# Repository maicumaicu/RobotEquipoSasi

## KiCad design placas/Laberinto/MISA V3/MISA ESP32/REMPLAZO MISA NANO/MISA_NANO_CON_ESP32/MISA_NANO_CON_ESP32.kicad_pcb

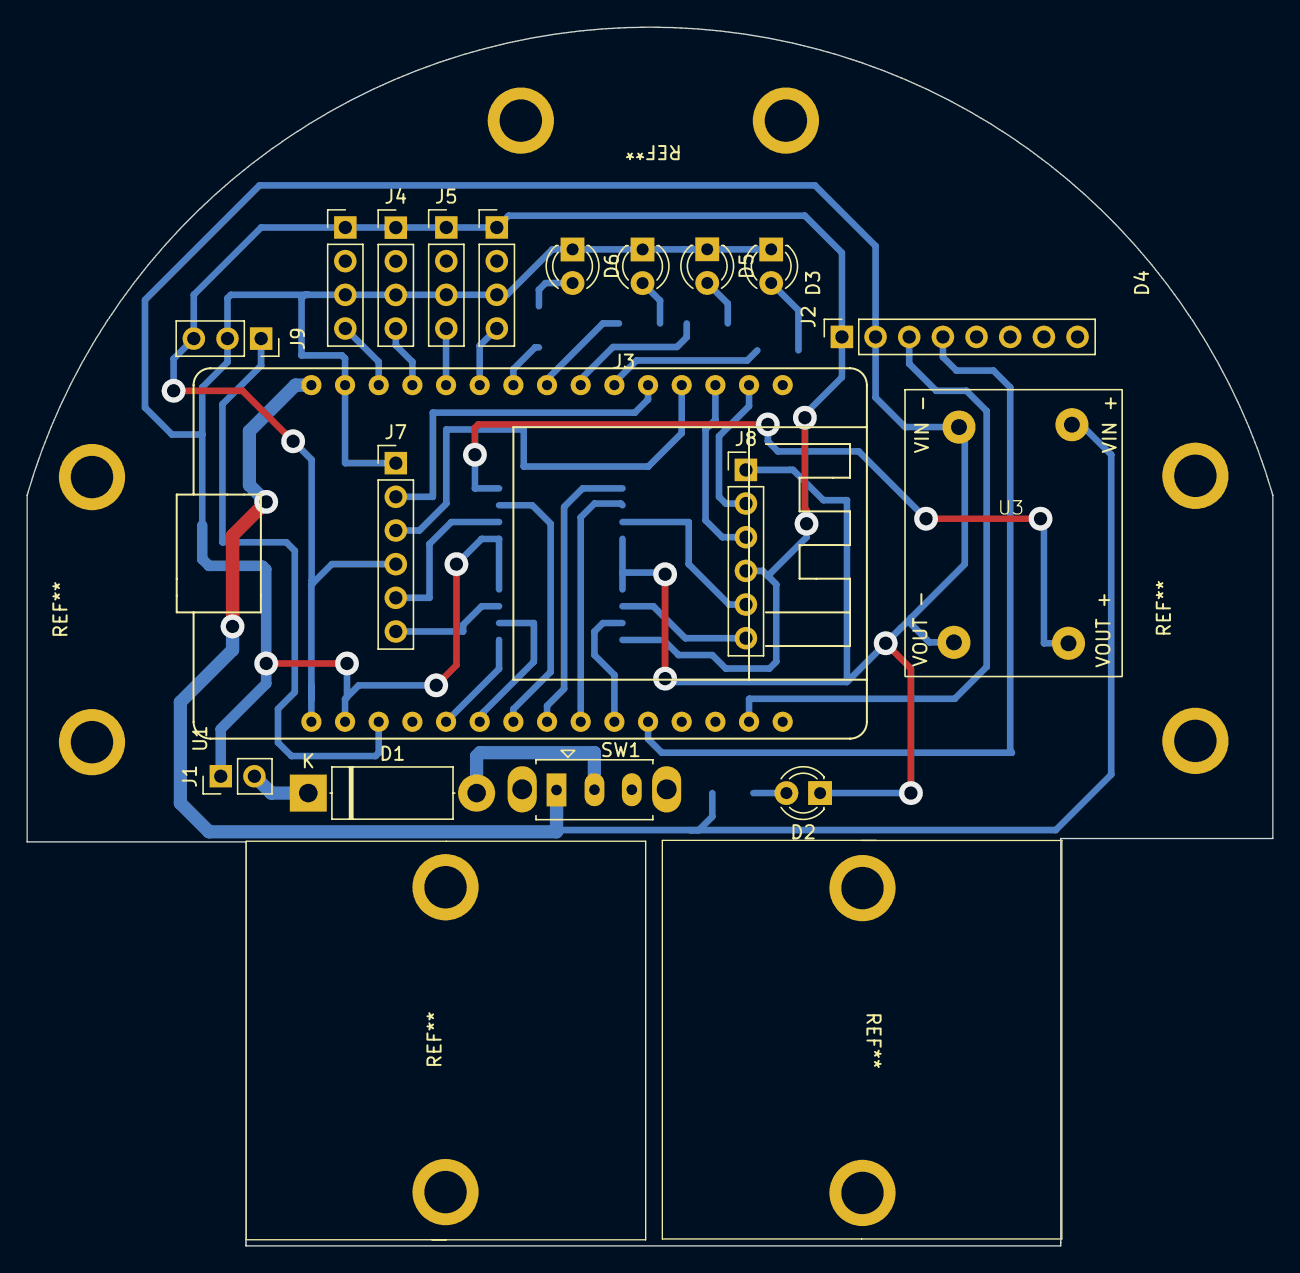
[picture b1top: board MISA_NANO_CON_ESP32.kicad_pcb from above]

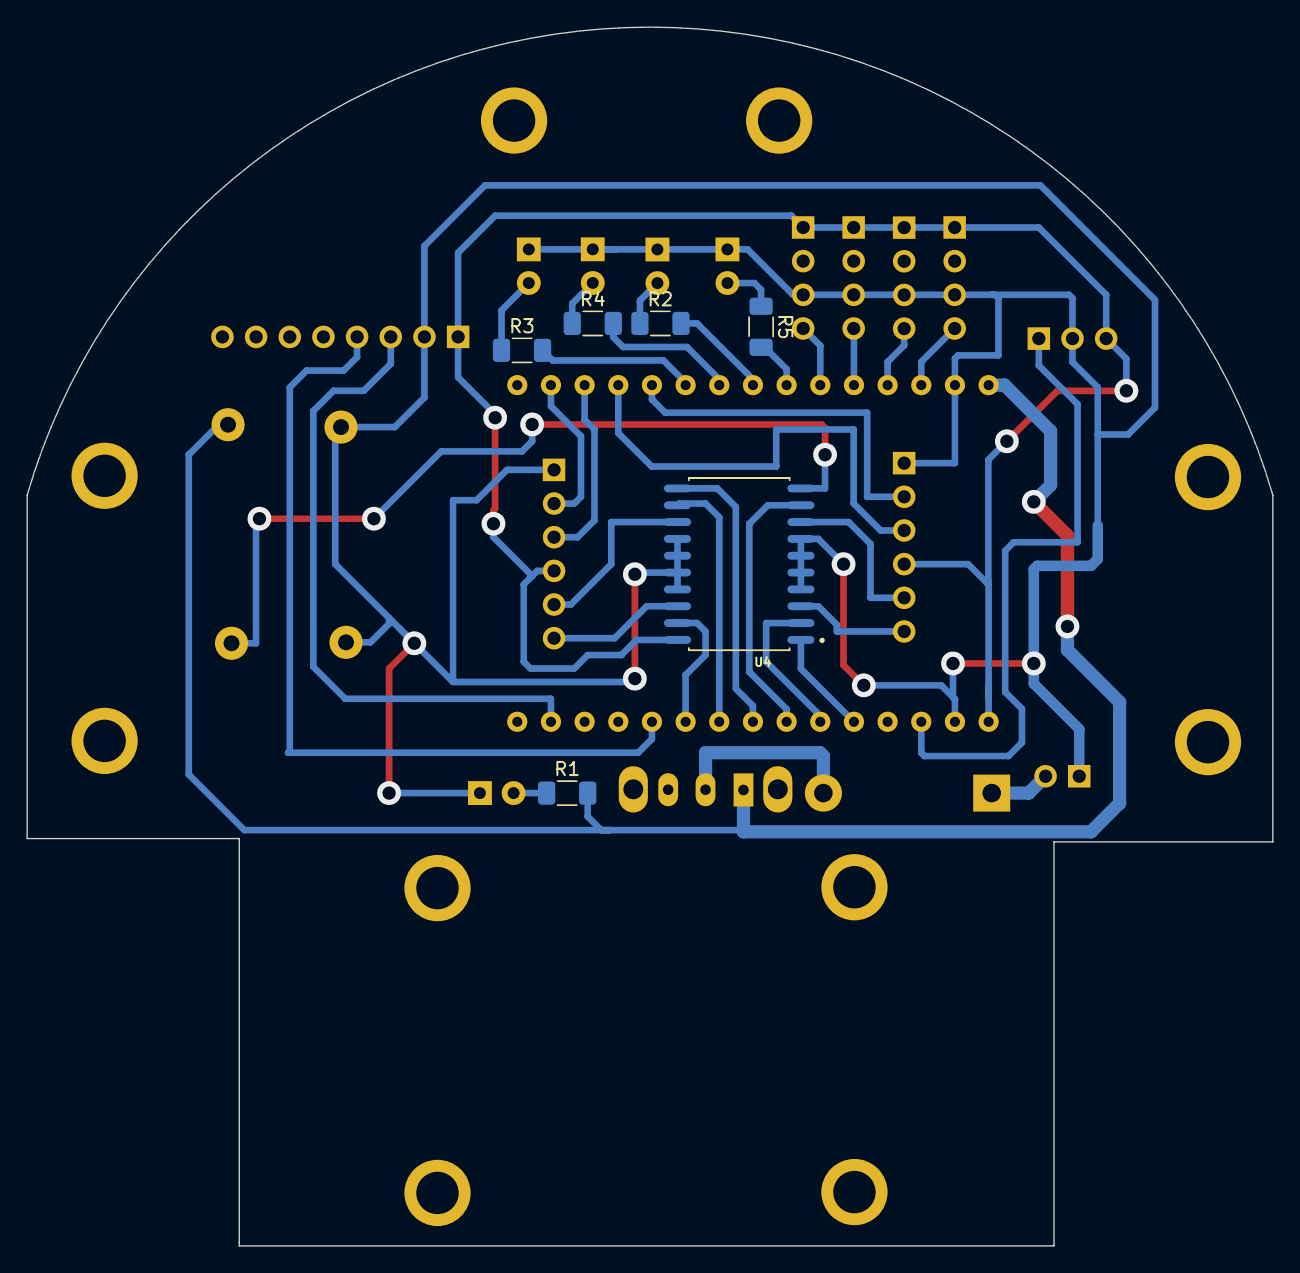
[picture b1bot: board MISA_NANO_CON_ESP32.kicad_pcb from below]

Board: 2 copper layers, 94.0 x 91.9 mm, 24 parts (6 on the bottom side), 36 nets.

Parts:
D1: type="D" model="DIODE" lib=""; D_5W_P12.70mm_Horizontal
D2, D3, D4, D5, D6: LED; LED_D3.0mm
J1: Conn_01x02_Male; PinHeader_1x02_P2.54mm_Vertical
J2: Conn_01x08_Female; PinSocket_1x08_P2.54mm_Vertical
J3, J4, J5, J6: Conn_01x04_Male; PinHeader_1x04_P2.54mm_Vertical
J7, J8: Conn_01x06_Female; PinHeader_1x06_P2.54mm_Vertical
J9: Conn_01x03_Socket; PinSocket_1x03_P2.54mm_Vertical
R1, R2, R3, R4, R5: R; R_1206_3216Metric_Pad1.30x1.75mm_HandSolder
SW1: SW_DPDT_x2; SW_Slide_1P2T_CK_OS102011MS2Q
U1: ESP32-Devkit-V1; DOIT_ESP32_Devkit
U3: Mt3608; Sx1308
U4: L293DD; SOIC127P1032X265-20N

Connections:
/3.3V: J2.1, J3.1, J4.1, J5.1, J6.1, J7.4, J8.4, J9.3, U1.30 (3v3), U4.20 (VSS)
/AO1: J7.6, U4.3 (OUTPUT_1)
/AO2: J7.5, U4.8 (OUTPUT_2)
/BO1: J8.5, U4.13 (OUTPUT_3)
/BO2: J8.6, U4.18 (OUTPUT_4)
/CNY70: J6.4, U1.3 (IO13)
/INA1: U1.25 (IO16), U4.2 (INPUT_1)
/INA2: U1.24 (IO17), U4.9 (INPUT_2)
/INB1: U1.21 (IO19), U4.19 (INPUT_4)
/INB2: U1.22 (IO18), U4.12 (INPUT_3)
/IR: J9.1, U1.28 (IO15)
/L1: R2.2, U1.8 (IO25)
/L2: R3.2, U1.10 (IO32)
/L3: R4.2, U1.9 (IO33)
/L4: R5.2, U1.7 (IO26)
/MA1: J7.2, U1.11 (IO35)
/MA2: J7.3, U1.12 (IO34)
/MB1: J8.2, U1.14 (IO36)
/MB2: J8.3, U1.13 (IO39)
/PWM1: U1.26 (IO4), U4.1 (ENABLE_1)
/PWM2: U1.23 (IO5), U4.11 (ENABLE_2)
/SCL: J2.3, U1.17 (IO22)
/SDA: J2.4, U1.20 (IO21)
/SHARP_C: J5.4, U1.5 (IO14)
/SHARP_D: J3.4, U1.6 (IO27)
/SHARP_I: J4.4, U1.4 (IO12)
/VIn: R1.2, SW1.1 (A), U1.1 (Vin), U3.1 (VIN+)
/Vm: U3.2 (VOUT+), U4.10 (VS)
GND: D2.1 (K), D3.1 (K), D4.1 (K), D5.1 (K), D6.1 (K), J1.1, J2.2, J3.3, J4.3, J5.3, J6.3, J7.1, J8.1, J9.2, U1.2 (GND), U1.29 (GND), U3.3 (VIN-), U3.4 (VOUT-), U4.4 (GND), U4.5 (GND), U4.6 (GND), U4.7 (GND), U4.14 (GND), U4.15 (GND), U4.16 (GND), U4.17 (GND)
unnamed: D1.1 (A), J1.2
unnamed: D1.2 (K), SW1.2 (B)
unnamed: D2.2 (A), R1.1
unnamed: D3.2 (A), R2.1
unnamed: D4.2 (A), R3.1
unnamed: D5.2 (A), R4.1
unnamed: D6.2 (A), R5.1

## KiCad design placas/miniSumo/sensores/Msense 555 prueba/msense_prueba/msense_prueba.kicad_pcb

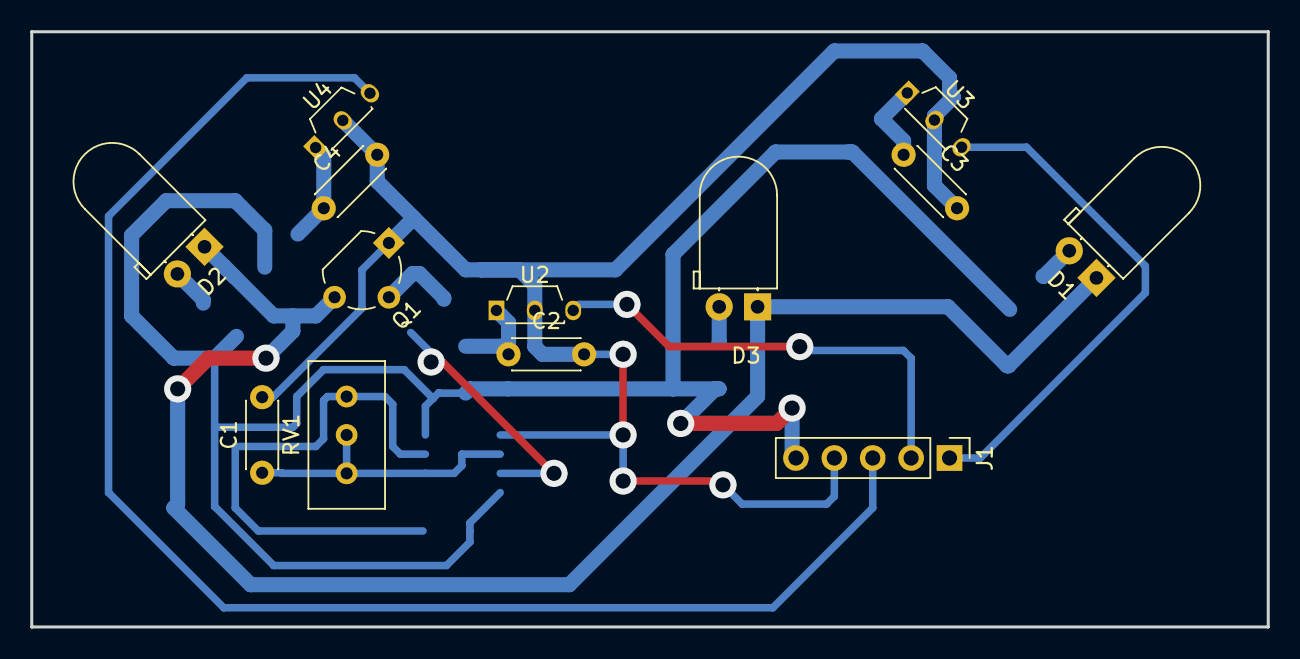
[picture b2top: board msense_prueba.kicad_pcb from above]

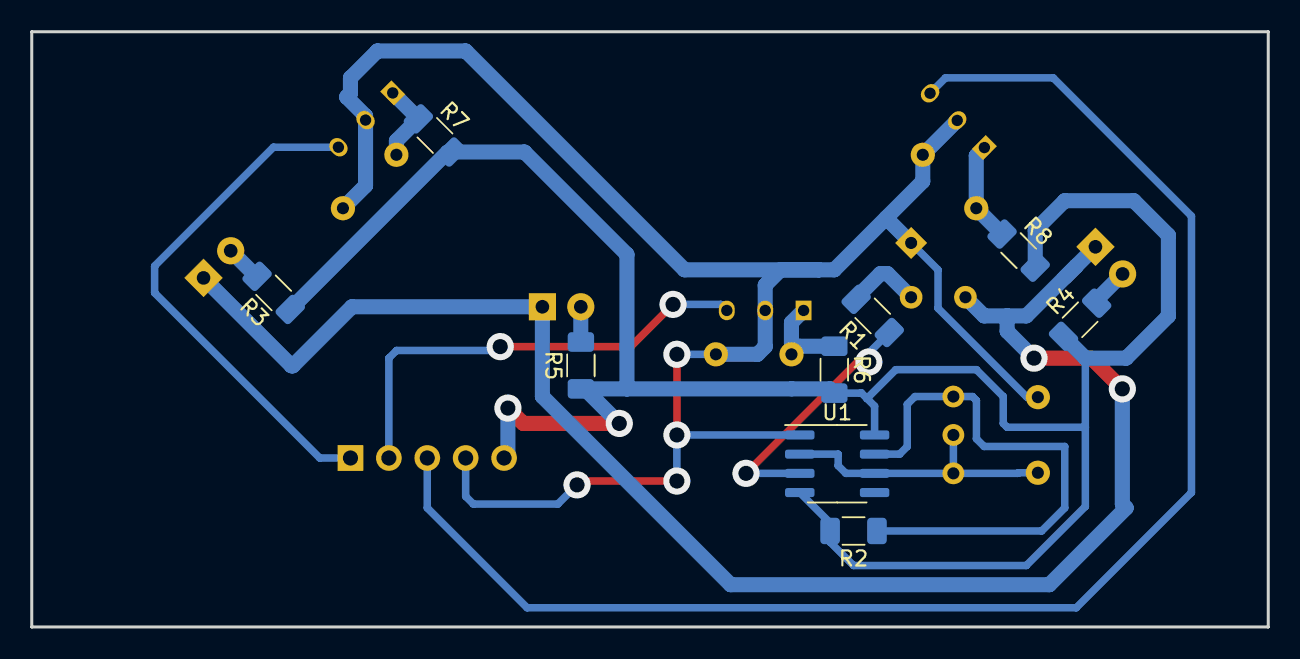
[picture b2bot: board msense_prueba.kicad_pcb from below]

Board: 2 copper layers, 81.8 x 39.4 mm, 22 parts (9 on the bottom side), 16 nets.

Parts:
C1: 102; C_Disc_D4.3mm_W1.9mm_P5.00mm
C2, C3, C4: 104; C_Disc_D4.3mm_W1.9mm_P5.00mm
D1, D2, D3: LED; LED_D5.0mm_Horizontal_O1.27mm_Z3.0mm
J1: Conn_01x05_Pin; PinHeader_1x05_P2.54mm_Vertical
Q1: BC547; TO-92_Wide
R1: 4.7k; R_1206_3216Metric_Pad1.30x1.75mm_HandSolder
R2: 1k8; R_1206_3216Metric_Pad1.30x1.75mm_HandSolder
R3, R4, R5, R6, R7, R8: 100; R_1206_3216Metric_Pad1.30x1.75mm_HandSolder
RV1: pote; Potentiometer_Bourns_3296W_Vertical
U1: LM555xM; SOIC-8_3.9x4.9mm_P1.27mm
U2, U3, U4: TSOP17xx; TO-92S_Wide

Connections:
38khz: D1.1 (K), D2.1 (K), D3.1 (K), Q1.3 (E)
+5V: J1.5, R2.2, R3.1, R4.1, R5.1, R6.2, R7.2, R8.2, U1.4 (R), U1.8 (VCC)
/S1: J1.3, U4.3 (OUT)
/S2: J1.2, U2.3 (OUT)
/S3: J1.1, U3.3 (OUT)
GND: C1.2, C2.2, C3.2, C4.2, J1.4, Q1.1 (C), U1.1 (GND), U2.2 (Vs), U3.2 (Vs), U4.2 (Vs)
unnamed: D1.2 (A), R3.2
unnamed: D2.2 (A), R4.2
unnamed: D3.2 (A), R5.2
unnamed: Q1.2 (B), R1.2
unnamed: R2.1, RV1.1, U1.7 (DIS)
unnamed: R1.1, U1.3 (Q)
unnamed: C1.1, RV1.2, RV1.3, U1.2 (TR), U1.6 (THR)
unnamed: C2.1, R6.1, U2.1 (GND)
unnamed: C3.1, R7.1, U3.1 (GND)
unnamed: C4.1, R8.1, U4.1 (GND)

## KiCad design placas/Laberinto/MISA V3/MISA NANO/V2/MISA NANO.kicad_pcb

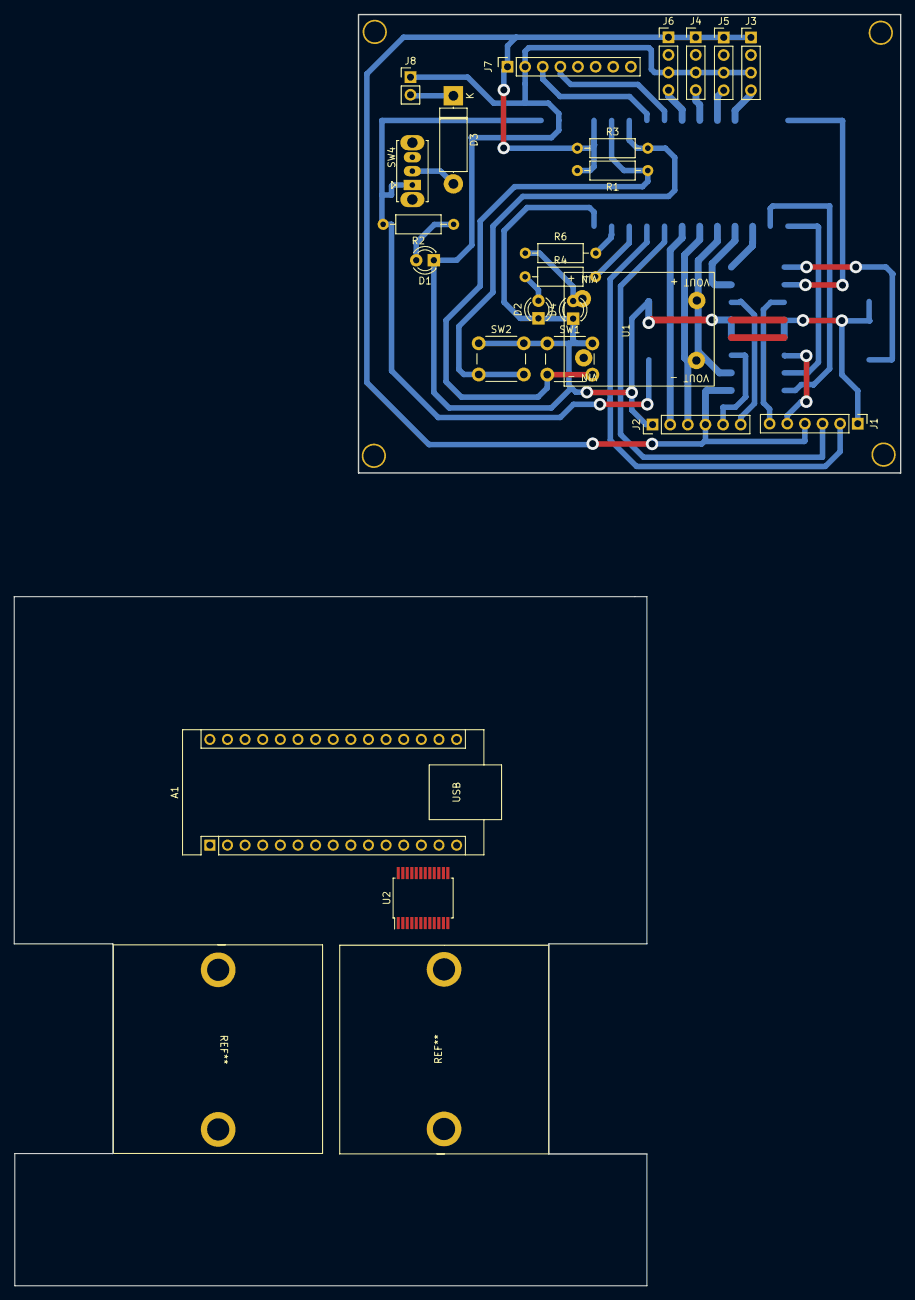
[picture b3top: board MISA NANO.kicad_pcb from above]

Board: 2 copper layers, 78.1 x 66.1 mm, 23 parts (0 on the bottom side), 33 nets.

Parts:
A1: Arduino_Nano_v3.x; Arduino_Nano
D1, D2, D4: LED; LED_D3.0mm
D3: type="D" model="DIODE" lib=""; D_5W_P12.70mm_Horizontal
J1, J2: Conn_01x06_Female; PinHeader_1x06_P2.54mm_Vertical
J3, J4, J5, J6: Conn_01x04_Male; PinHeader_1x04_P2.54mm_Vertical
J7: Conn_01x08_Female; PinSocket_1x08_P2.54mm_Vertical
J8: Conn_01x02_Male; PinHeader_1x02_P2.54mm_Vertical
R1, R2, R3, R4, R6: R; R_Axial_DIN0207_L6.3mm_D2.5mm_P10.16mm_Horizontal
SW1, SW2: SW_Push; SW_PUSH_6mm
SW4: SW_DPDT_x2; SW_Slide_1P2T_CK_OS102011MS2Q
U1: Mt3608; Sx1308
U2: TB6612FNG; SSOP-24_5.3x8.2mm_P0.65mm

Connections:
/5v: A1.27 (+5V), J1.4, J2.4, J3.1, J4.1, J5.1, J6.1, J7.1, R1.2, R3.1, U2.20 (VCC)
/AO1: J1.5, U2.1 (AO1), U2.2 (AO1)
/AO2: J1.6, U2.5 (AO2), U2.6 (AO2)
/BO1: J2.6, U2.11 (BO1), U2.12 (BO1)
/BO2: J2.5, U2.7 (BO2), U2.8 (BO2)
/BTN1: A1.26 (A7), R1.1, SW1.2
/BTN2: A1.25 (A6), R3.2, SW2.2
/CNY70: A1.22 (A3), J6.4
/INA1: A1.15 (D12), U2.21 (AIN1)
/INA2: A1.16 (D13), U2.22 (AIN2)
/INB1: A1.12 (D9), U2.17 (BIN1)
/INB2: A1.11 (D8), U2.16 (BIN2)
/Led: A1.6 (D3), R4.2
/Led2: A1.5 (D2), R6.2
/MA1: A1.7 (D4), J1.2
/MA2: A1.8 (D5), J1.3
/MB1: A1.9 (D6), J2.2
/MB2: A1.10 (D7), J2.3
/PWM1: A1.14 (D11), U2.23 (PWMA)
/PWM2: A1.13 (D10), U2.15 (PWMB)
/SCL: A1.24 (A5), J7.3
/SDA: A1.23 (A4), J7.4
/SHARP_C: A1.20 (A1), J5.4
/SHARP_D: A1.19 (A0), J3.4
/SHARP_I: A1.21 (A2), J4.4
/VIn: A1.30 (VIN), R2.2, SW4.1 (A), U1.1 (VIN+)
/Vm: U1.2 (VOUT+), U2.13 (VM2), U2.14 (VM3), U2.24 (VM1)
GND: A1.4 (GND), A1.29 (GND), D1.1 (K), D2.1 (K), D4.1 (K), J1.1, J2.1, J3.3, J4.3, J5.3, J6.3, J7.2, J8.1, SW1.1, SW2.1, U1.3 (VIN-), U1.4 (VOUT-), U2.3 (PGND1), U2.4 (PGND1), U2.9 (PGND2), U2.10 (PGND2), U2.18 (GND)
unnamed: D1.2 (A), R2.1
unnamed: D2.2 (A), R4.1
unnamed: D3.1 (A), J8.2
unnamed: D3.2 (K), SW4.2 (B)
unnamed: D4.2 (A), R6.1

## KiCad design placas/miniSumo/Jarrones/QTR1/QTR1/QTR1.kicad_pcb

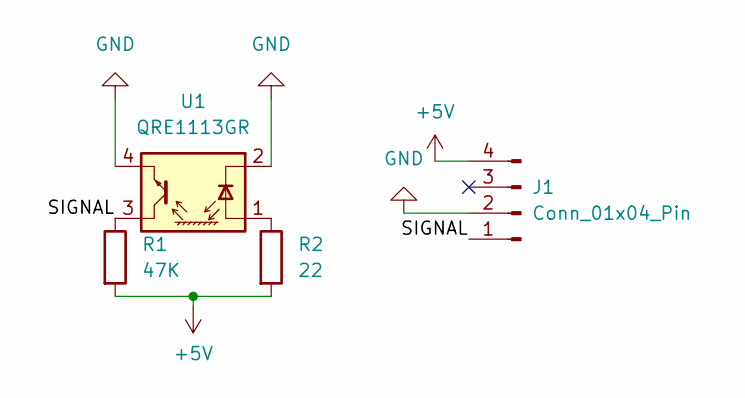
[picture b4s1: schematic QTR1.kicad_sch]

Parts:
J1: Conn_01x04_Pin; PinHeader_1x04_P2.54mm_Horizontal
R1: 47K; R_1206_3216Metric_Pad1.30x1.75mm_HandSolder
R2: 22; R_1206_3216Metric_Pad1.30x1.75mm_HandSolder
U1: QRE1113GR; OnSemi_CASE100CY

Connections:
+5V: J1.4, R1.2, R2.2
/SIGNAL: J1.1, R1.1, U1.3
GND: J1.2, U1.2 (K), U1.4
unnamed: R2.1, U1.1 (A)

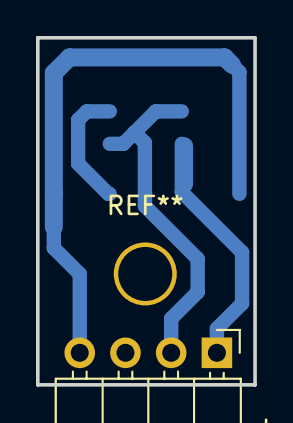
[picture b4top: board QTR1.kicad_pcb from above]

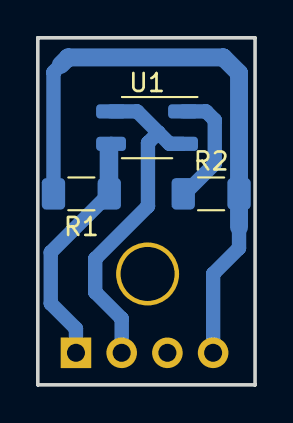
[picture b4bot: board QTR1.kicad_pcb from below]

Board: 2 copper layers, 12.1 x 19.3 mm, 4 parts (3 on the bottom side), 4 nets.

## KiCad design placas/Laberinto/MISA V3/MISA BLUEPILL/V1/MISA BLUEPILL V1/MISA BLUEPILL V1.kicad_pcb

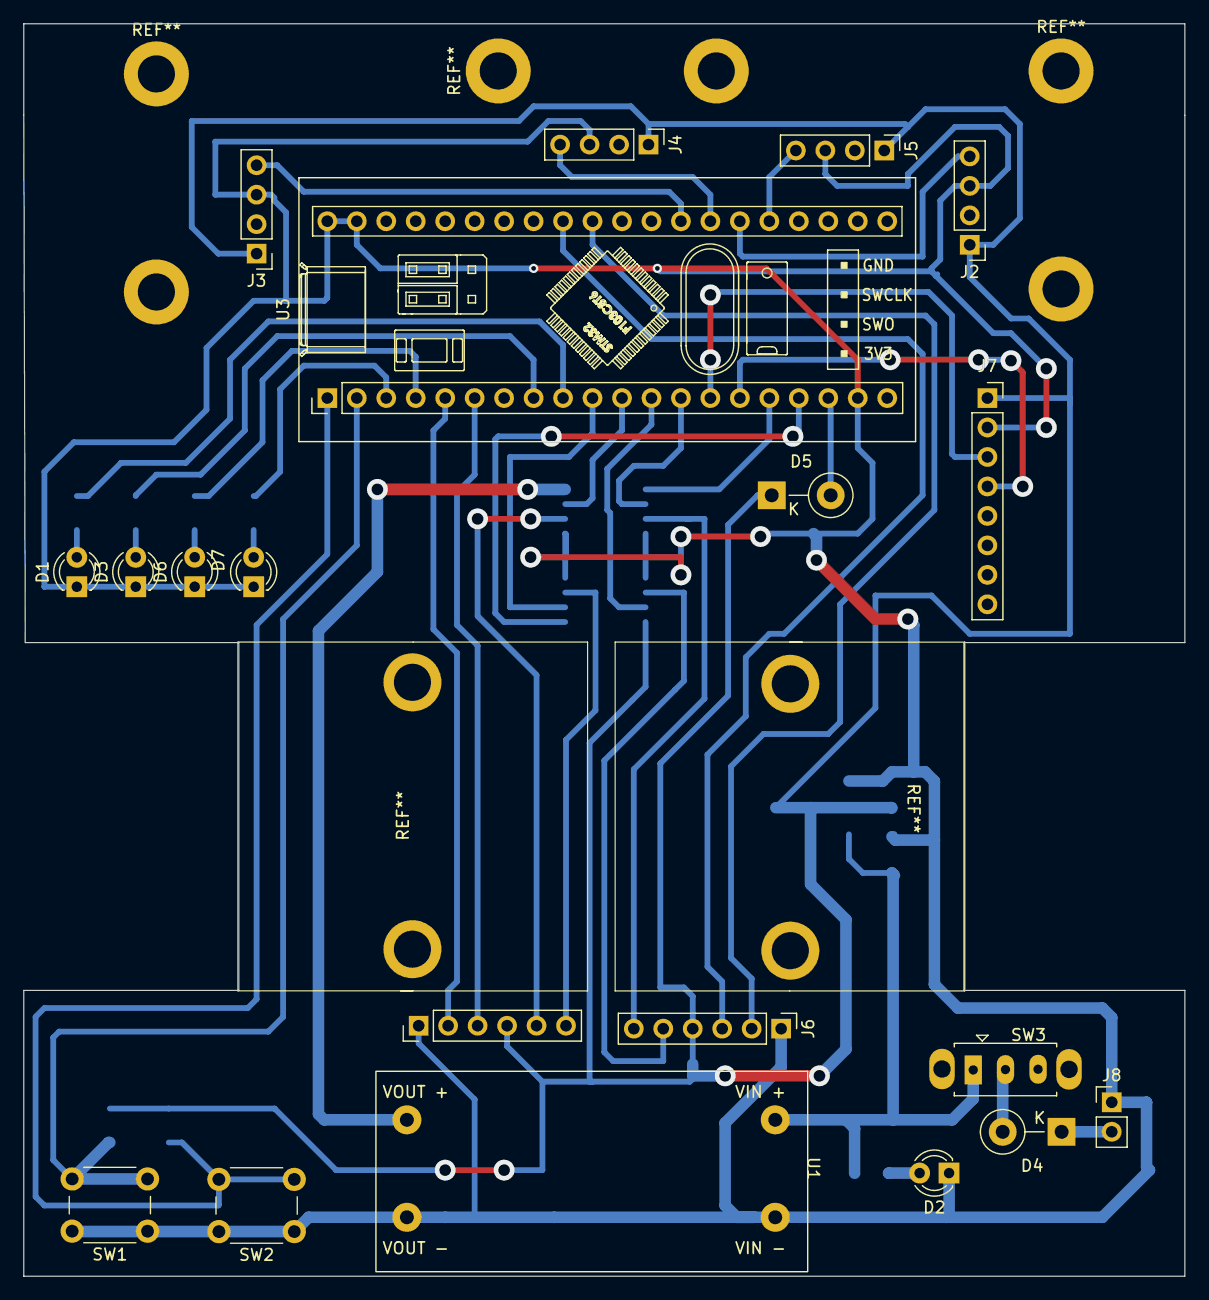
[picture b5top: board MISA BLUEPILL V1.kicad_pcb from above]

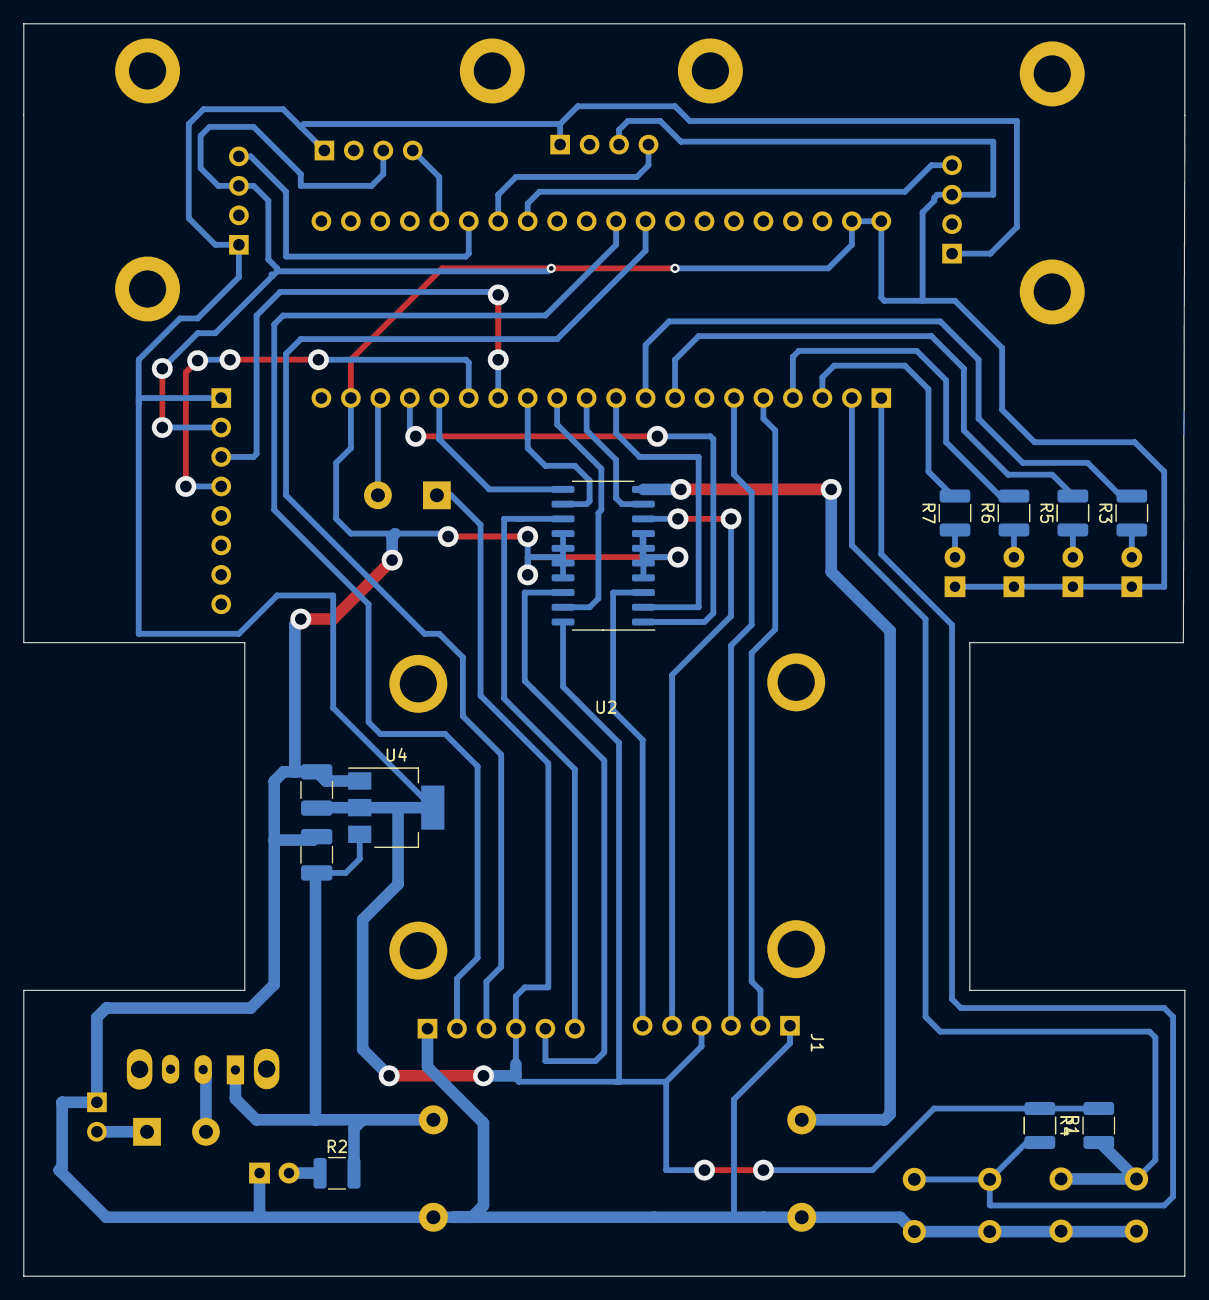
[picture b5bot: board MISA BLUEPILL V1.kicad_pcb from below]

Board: 2 copper layers, 100.1 x 107.9 mm, 31 parts (11 on the bottom side), 38 nets.

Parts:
C1, C2: C_Polarized; C_1210_3225Metric_Pad1.33x2.70mm_HandSolder
D1, D2, D3, D6, D7: LED; LED_D3.0mm
D4, D5: type="D" model="DIODE" lib=""; D_DO-15_P5.08mm_Vertical_KathodeUp
J1, J6: Conn_01x06_Female; PinHeader_1x06_P2.54mm_Vertical
J2, J3, J4, J5: Conn_01x04_Male; PinHeader_1x04_P2.54mm_Vertical
J7: Conn_01x08_Female; PinSocket_1x08_P2.54mm_Vertical
J8: Conn_01x02_Male; PinHeader_1x02_P2.54mm_Vertical
R1, R2, R3, R4, R5, R6, R7: R; R_1210_3225Metric
SW1, SW2: SW_Push; SW_PUSH_6mm
SW3: SW_DPDT_x2; SW_Slide_1P2T_CK_OS102011MS2Q
U1: Mt3608; MT3608
U2: L293; SO-20_5.3x12.6mm_P1.27mm
U3: YAAJ_BluePill_Part_Like_SWD_Breakout; YAAJ_BluePill_1
U4: AMS1117-5.0; SOT-223-3_TabPin2

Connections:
/5v: C2.1, D5.1 (A), J1.4, J2.1, J3.1, J4.1, J5.1, J6.4, J7.1, R1.2, R4.1, U2.20 (VCC1), U4.2 (VO)
/AO1: J1.5, U2.8 (2Y)
/AO2: J1.6, U2.3 (1Y)
/BO1: J6.6, U2.13 (3Y)
/BO2: J6.5, U2.18 (4Y)
/BTN1: R1.1, SW1.2, U3.2 (PB13)
/BTN2: R4.2, SW2.2, U3.1 (PB12)
/CNY70: J5.4, U3.25 (PA0)
/INA1: U2.2 (1A), U3.10 (PA15)
/INA2: U2.9 (2A), U3.11 (PB3)
/INB1: U2.12 (3A), U3.13 (PB5)
/INB2: U2.19 (4A), U3.12 (PB4)
/Led: R5.2, U3.8 (PA11)
/Led2: R3.2, U3.9 (PA12)
/Led3: R6.2, U3.4 (PB15)
/Led4: R7.2, U3.3 (PB14)
/MA1: J1.2, U3.5 (PA8)
/MA2: J1.3, U3.6 (PA9)
/MB1: J6.2, U3.31 (PA6)
/MB2: J6.3, U3.32 (PA7)
/PWM1: U2.1 (EN1,2), U3.17 (PB9)
/PWM2: U2.11 (EN3,4), U3.16 (PB8)
/SCL: J7.3, U3.14 (PB6)
/SDA: J7.4, U3.15 (PB7)
/SHARP_C: J4.4, U3.27 (PA2)
/SHARP_D: J2.4, U3.26 (PA1)
/SHARP_I: J3.4, U3.28 (PA3)
/VIn: C1.1, R2.2, SW3.1 (A), U1.1 (VIN+), U4.3 (VI)
/Vm: U1.2 (VOUT+), U2.10 (VCC2)
GND: C1.2, C2.2, D1.1 (K), D2.1 (K), D3.1 (K), D6.1 (K), D7.1 (K), J1.1, J2.3, J3.3, J4.3, J5.3, J6.1, J7.2, J8.1, SW1.1, SW2.1, U1.3 (VIN-), U1.4 (VOUT-), U2.4 (GND), U2.5 (GND), U2.6 (GND), U2.7 (GND), U2.14 (GND), U2.15 (GND), U2.16 (GND), U2.17 (GND), U3.19 (GND), U3.39 (GND), U3.40 (GND), U4.1 (GND)
unnamed: D1.2 (A), R3.1
unnamed: D2.2 (A), R2.1
unnamed: D3.2 (A), R5.1
unnamed: D4.1 (A), J8.2
unnamed: D4.2 (K), SW3.2 (B)
unnamed: D5.2 (K), U3.18 (5V)
unnamed: D6.2 (A), R6.1
unnamed: D7.2 (A), R7.1

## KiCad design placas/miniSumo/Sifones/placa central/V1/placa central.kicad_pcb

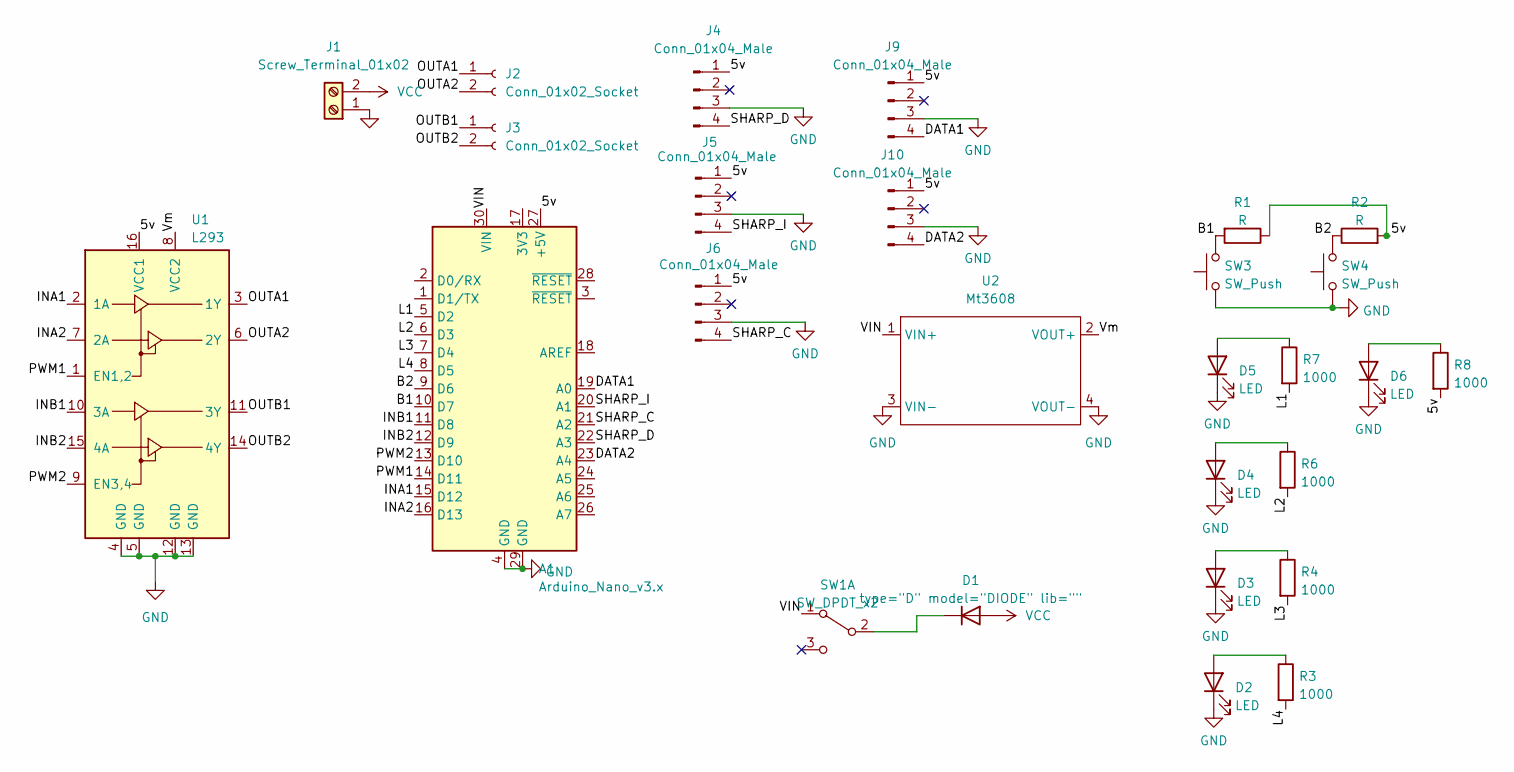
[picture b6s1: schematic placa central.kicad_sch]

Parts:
A1: Arduino_Nano_v3.x; Arduino_Nano
D1: type="D" model="DIODE" lib=""; D_5W_P5.08mm_Vertical_AnodeUp
D2, D3, D4, D5, D6: LED; LED_D3.0mm
J1: Screw_Terminal_01x02; PinSocket_1x02_P2.54mm_Vertical
J2, J3: Conn_01x02_Socket; PinSocket_1x02_P2.54mm_Vertical
J4, J5, J6, J9, J10: Conn_01x04_Male; PinHeader_1x04_P2.54mm_Vertical
R1, R2: R; R_1206_3216Metric_Pad1.30x1.75mm_HandSolder
R3, R4, R6, R7, R8: 1000; R_1206_3216Metric_Pad1.30x1.75mm_HandSolder
SW1: SW_DPDT_x2; SW_Slide_1P2T_CK_OS102011MS2Q
SW3, SW4: SW_Push; SW_PUSH_6mm
U1: L293; DIP-16_W7.62mm
U2: Mt3608; MT3608

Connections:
/5v: A1.27 (+5V), J4.1, J5.1, J6.1, J9.1, J10.1, R1.1, R2.2, R8.2, U1.16 (VCC1)
/B1: A1.10 (D7), R1.2, SW3.2
/B2: A1.9 (D6), R2.1, SW4.2
/DATA1: A1.19 (A0), J9.4
/DATA2: A1.23 (A4), J10.4
/INA1: A1.15 (D12), U1.2 (1A)
/INA2: A1.16 (D13), U1.7 (2A)
/INB1: A1.11 (D8), U1.10 (3A)
/INB2: A1.12 (D9), U1.15 (4A)
/L1: A1.5 (D2), R7.2
/L2: A1.6 (D3), R6.2
/L3: A1.7 (D4), R4.2
/L4: A1.8 (D5), R3.2
/OUTA1: J2.1, U1.3 (1Y)
/OUTA2: J2.2, U1.6 (2Y)
/OUTB1: J3.1, U1.11 (3Y)
/OUTB2: J3.2, U1.14 (4Y)
/PWM1: A1.14 (D11), U1.1 (EN1,2)
/PWM2: A1.13 (D10), U1.9 (EN3,4)
/SHARP_C: A1.21 (A2), J6.4
/SHARP_D: A1.22 (A3), J4.4
/SHARP_I: A1.20 (A1), J5.4
/VIN: A1.30 (VIN), SW1.1 (A), U2.1 (VIN+)
/Vm: U1.8 (VCC2), U2.2 (VOUT+)
GND: A1.4 (GND), A1.29 (GND), D2.1 (K), D3.1 (K), D4.1 (K), D5.1 (K), D6.1 (K), J1.1, J4.3, J5.3, J6.3, J9.3, J10.3, SW3.1, SW4.1, U1.4 (GND), U1.5 (GND), U1.12 (GND), U1.13 (GND), U2.3 (VIN-), U2.4 (VOUT-)
unnamed: D1.2 (K), SW1.2 (B)
unnamed: D2.2 (A), R3.1
unnamed: D3.2 (A), R4.1
unnamed: D4.2 (A), R6.1
unnamed: D5.2 (A), R7.1
unnamed: D6.2 (A), R8.1
VCC: D1.1 (A), J1.2

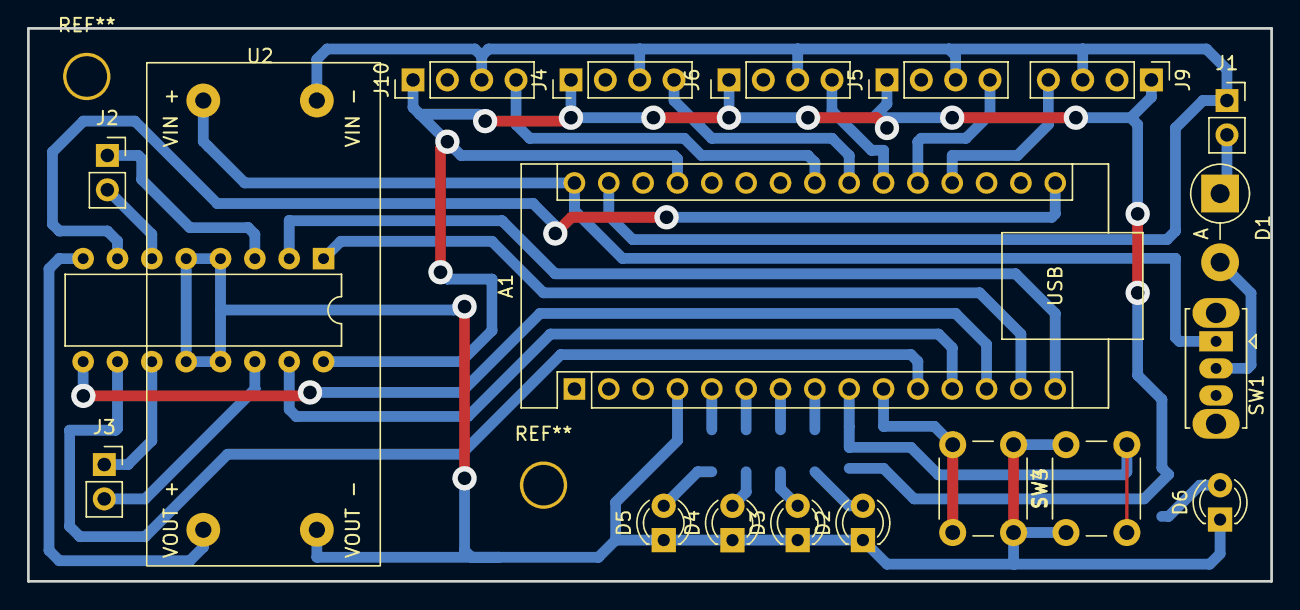
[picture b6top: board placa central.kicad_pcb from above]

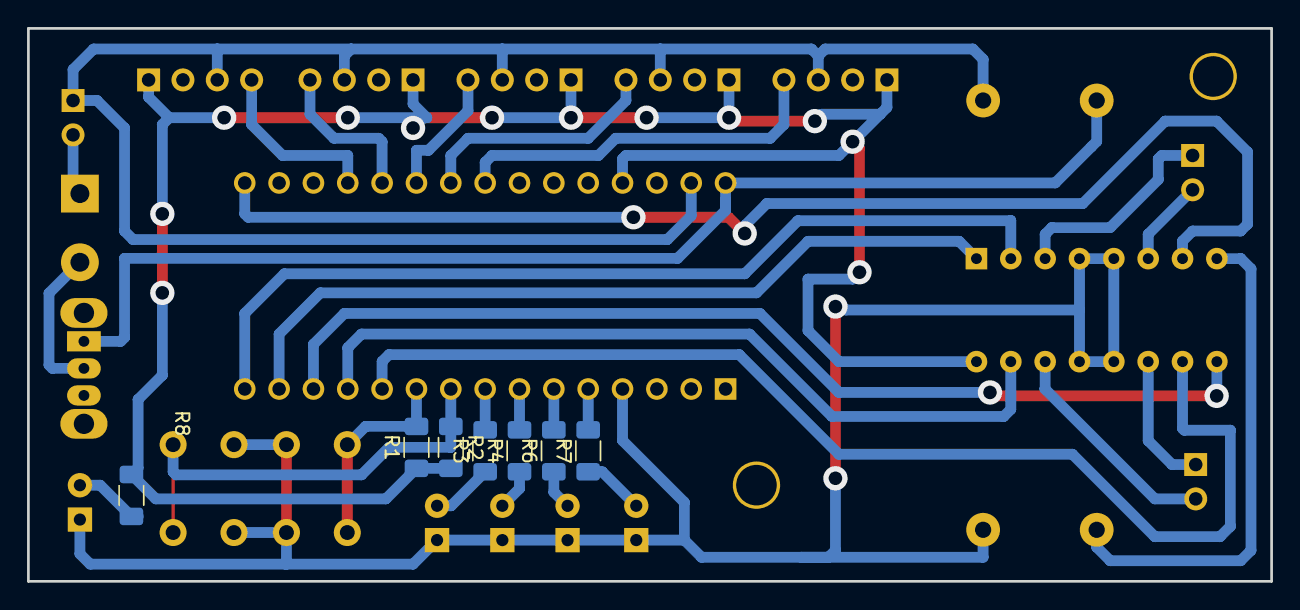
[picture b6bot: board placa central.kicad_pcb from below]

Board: 2 copper layers, 91.9 x 40.9 mm, 27 parts (7 on the bottom side), 32 nets.

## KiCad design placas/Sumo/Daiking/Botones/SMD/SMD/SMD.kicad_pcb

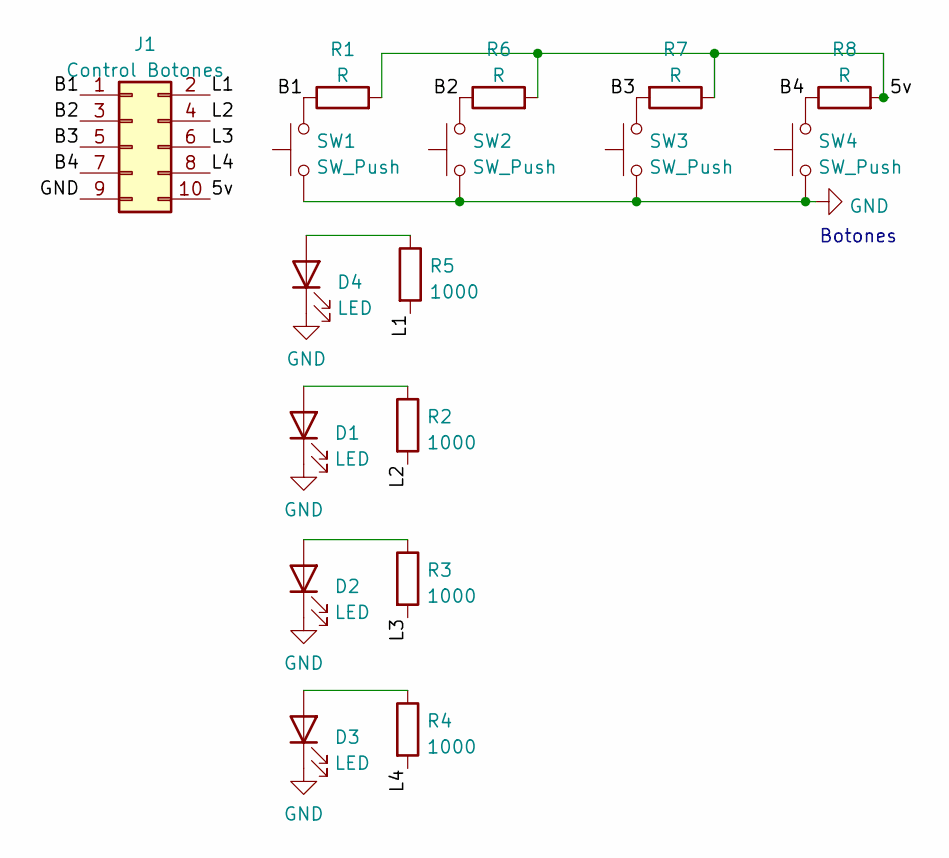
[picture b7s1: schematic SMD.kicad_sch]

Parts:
D1, D2, D3, D4: LED
J1: Control Botones; IDC-Header_2x05_P2.54mm_Vertical
R1, R6, R7, R8: R
R2, R3, R4, R5: 1000
SW1, SW2, SW3, SW4: SW_Push

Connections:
/5v: J1.10, R1.2, R6.2, R7.1, R8.2
/B1: J1.1, R1.1, SW1.2
/B2: J1.3, R6.1, SW2.2
/B3: J1.5, R7.2, SW3.2
/B4: J1.7, R8.1, SW4.2
/L1: J1.2, R5.2
/L2: J1.4, R2.2
/L3: J1.6, R3.2
/L4: J1.8, R4.2
GND: D1.1 (K), D2.1 (K), D3.1 (K), D4.1 (K), J1.9, SW1.1, SW2.1, SW3.1, SW4.1
unnamed: D1.2 (A), R2.1
unnamed: D2.2 (A), R3.1
unnamed: D3.2 (A), R4.1
unnamed: D4.2 (A), R5.1

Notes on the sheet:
Botones

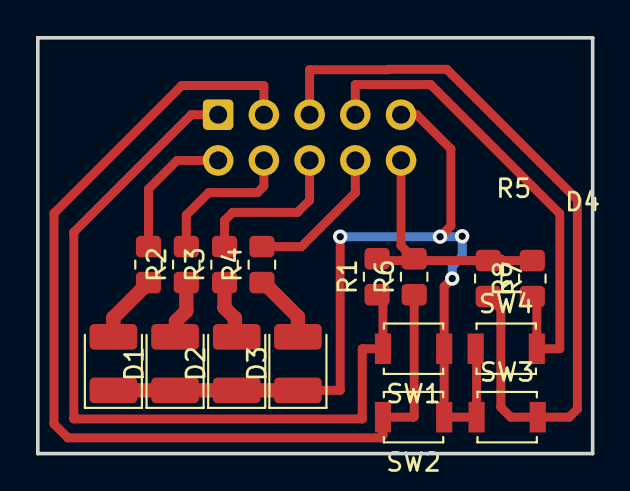
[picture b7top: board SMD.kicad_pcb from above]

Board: 2 copper layers, 30.8 x 23.1 mm, 17 parts (1 on the bottom side), 14 nets.

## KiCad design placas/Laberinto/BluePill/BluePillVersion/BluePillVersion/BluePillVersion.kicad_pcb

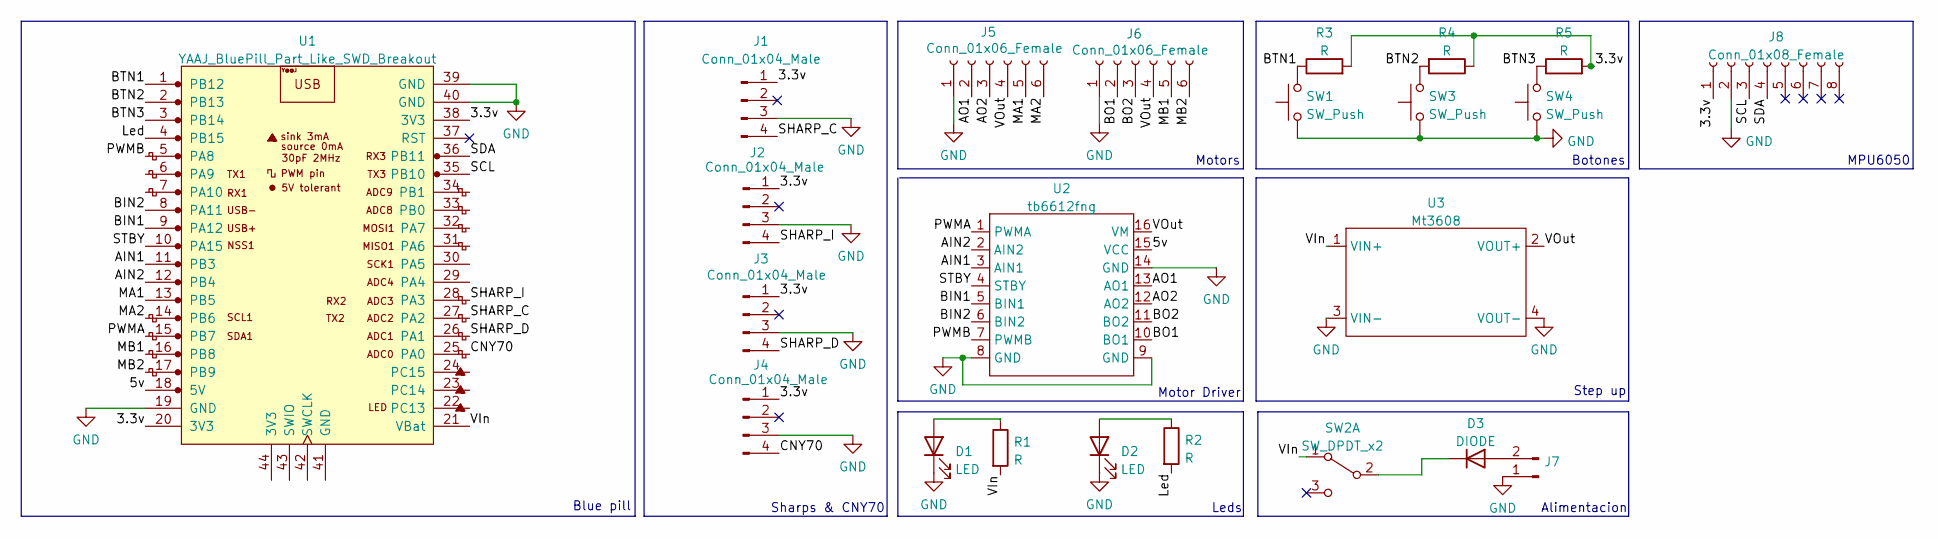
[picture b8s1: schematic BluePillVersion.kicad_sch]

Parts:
D1, D2: LED; LED_D3.0mm
D3: DIODE; D_5W_P12.70mm_Horizontal
J1, J2, J3, J4: Conn_01x04_Male; PinHeader_1x04_P2.54mm_Vertical
J5, J6: Conn_01x06_Female; PinSocket_1x06_P2.54mm_Vertical
J7: Conn_01x02_Male; PinHeader_1x02_P2.54mm_Vertical
J8: Conn_01x08_Female; PinSocket_1x08_P2.54mm_Vertical
R1, R2, R3, R4, R5: R; R_Axial_DIN0207_L6.3mm_D2.5mm_P10.16mm_Horizontal
SW1, SW3, SW4: SW_Push; SW_PUSH_6mm
SW2: SW_DPDT_x2; SW_Slide_1P2T_CK_OS102011MS2Q
U1: YAAJ_BluePill_Part_Like_SWD_Breakout; YAAJ_BluePill_1
U2: tb6612fng
U3: Mt3608; MT3608

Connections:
/3.3v: J1.1, J2.1, J3.1, J4.1, J8.1, R3.2, R4.1, R5.2, U1.20 (3V3), U1.38 (3V3)
/5v: U1.18 (5V), U2.15 (VCC)
/AIN1: U1.11 (PB3), U2.3 (AIN1)
/AIN2: U1.12 (PB4), U2.2 (AIN2)
/AO1: J5.2, U2.13 (AO1)
/AO2: J5.3, U2.12 (AO2)
/BIN1: U1.9 (PA12), U2.5 (BIN1)
/BIN2: U1.8 (PA11), U2.6 (BIN2)
/BO1: J6.2, U2.10 (BO1)
/BO2: J6.3, U2.11 (BO2)
/BTN1: R3.1, SW1.2, U1.1 (PB12)
/BTN2: R4.2, SW3.2, U1.2 (PB13)
/BTN3: R5.1, SW4.2, U1.3 (PB14)
/CNY70: J4.4, U1.25 (PA0)
/Led: R2.2, U1.4 (PB15)
/MA1: J5.5, U1.13 (PB5)
/MA2: J5.6, U1.14 (PB6)
/MB1: J6.5, U1.16 (PB8)
/MB2: J6.6, U1.17 (PB9)
/PWMA: U1.15 (PB7), U2.1 (PWMA)
/PWMB: U1.5 (PA8), U2.7 (PWMB)
/SCL: J8.3, U1.35 (PB10)
/SDA: J8.4, U1.36 (PB11)
/SHARP_C: J1.4, U1.27 (PA2)
/SHARP_D: J3.4, U1.26 (PA1)
/SHARP_I: J2.4, U1.28 (PA3)
/STBY: U1.10 (PA15), U2.4 (STBY)
/VIn: R1.2, SW2.1 (A), U1.21 (VBat), U3.1 (VIN+)
/VOut: J5.4, J6.4, U2.16 (VM), U3.2 (VOUT+)
GND: D1.1 (K), D2.1 (K), J1.3, J2.3, J3.3, J4.3, J5.1, J6.1, J7.1, J8.2, SW1.1, SW3.1, SW4.1, U1.19 (GND), U1.39 (GND), U1.40 (GND), U2.8 (GND), U2.9 (GND), U2.14 (GND), U3.3 (VIN-), U3.4 (VOUT-)
unnamed: D1.2 (A), R1.1
unnamed: D2.2 (A), R2.1
unnamed: D3.1 (A), J7.2
unnamed: D3.2 (K), SW2.2 (B)

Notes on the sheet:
Motor Driver
Step up
MPU6050
Blue pill
Alimentacion
Leds
Motors
Sharps & CNY70
Botones
